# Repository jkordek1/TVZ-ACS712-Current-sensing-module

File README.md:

# TVZ ACS712 Current sensing module

 PCB module for ACS712, fully Integrated, Hall Effect-Based Linear Current Sensor with 2.1 kVRMS Voltage Isolation and a Low-Resistance Current Conductor.
 
 ## Features
 - 4mm banana plugs for sensors IP+ and IP- pins
 - 3 different capacitor values for filtering (switchable via jumper pins)
 - powering sensor via miniUSB or male pins
 - power LED
 - Probe clips for easy oscilloscope connections

## Images

## Project folder structure
    .
    ├── ...
    ├── Images                  # Images of the project
    ├── KiCADFiles              # Main folder
    │   ├── 3D models           # 3d models of components
    │   ├── Datasheet           # Datasheet collection
    │   ├── production          # gerber output folder
    │   ├── myDAQExpansionBoard # Main folder for KiCAD files
    │   └── Schematic.pdf       # Project schematic
    └── ...

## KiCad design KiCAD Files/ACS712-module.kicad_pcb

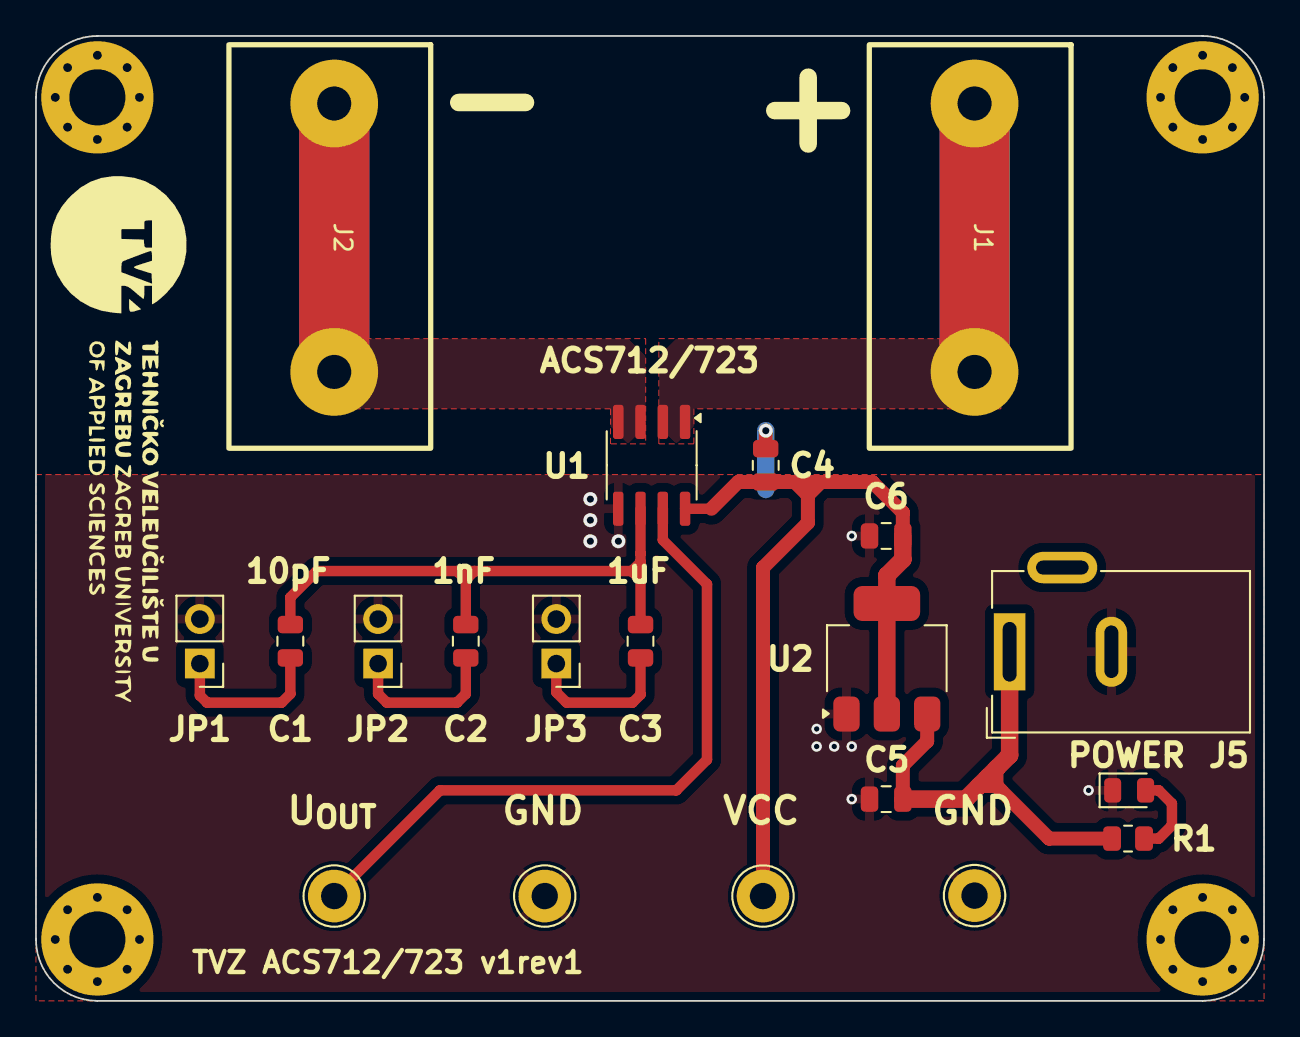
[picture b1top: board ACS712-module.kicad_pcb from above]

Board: 2 copper layers, 70.0 x 55.0 mm, 24 parts (0 on the bottom side), 11 nets.

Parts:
C1: 10p / 50V; C_0805_2012Metric
C2: 1n / 50V; C_0805_2012Metric
C3: 1u / 50V; C_0805_2012Metric
C4: 100n; C_0805_2012Metric
C5, C6: 10uF; C_0805_2012Metric
D1: RED; LED_0805_2012Metric
H1, H2, H3, H4: MountingHole_Pad; MountingHole_3.2mm_M3_Pad_Via
J1: Banana plug; DELTRON 4mm banana socket - red
J2: Banana plug; DELTRON 4mm banana socket - black
J5: Barrel_Jack_MountingPin; BarrelJack_Wuerth_6941xx301002
JP1, JP2, JP3: Jumper_2_Bridged; PinHeader_1x02_P2.54mm_Vertical
R1: 1k3; R_0805_2012Metric
TP1, TP2, TP3, TP4: TestPoint; KEYS4952
U1: ACS712; SOIC-8_3.9x4.9mm_P1.27mm
U2: AMS1117-5.0; SOT-223-3_TabPin2

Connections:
+5V: C4.1, C6.1, TP4.1, U1.8 (VCC), U2.2 (VO)
+12V: C5.1, J5.1, R1.1, U2.3 (VI)
/Vout: TP3.1, U1.7 (VIOUT)
GND: C4.2, C5.2, C6.2, D1.1 (K), J5.2, JP1.2 (B), JP2.2 (B), JP3.2 (B), TP1.1, TP2.1, U1.5 (GND), U2.1 (GND)
unnamed: D1.2 (A), R1.2
unnamed: J1.1, U1.1 (IP+), U1.2 (IP+)
unnamed: J2.1, U1.3 (IP-), U1.4 (IP-)
unnamed: C1.2, JP1.1 (A)
unnamed: C2.2, JP2.1 (A)
unnamed: C3.2, JP3.1 (A)
unnamed: C1.1, C2.1, C3.1, U1.6 (FILTER)

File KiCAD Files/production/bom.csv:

Designator,Footprint,Quantity,Value,LCSC Part #
C1,0805,1,10p / 50V,
C2,0805,1,1n / 50V,
C3,0805,1,1u / 50V,
C4,0805,1,100n,
"C5, C6",0805,2,10uF,
D1,0805,1,RED,
"H1, H2, H3, H4",MountingHole_3.2mm_M3_Pad_Via,4,MountingHole_Pad,
J1,DELTRON 4mm banana socket - red,1,Banana plug,
J2,DELTRON 4mm banana socket - black,1,Banana plug,
J5,BarrelJack_Wuerth_6941xx301002,1,Barrel_Jack_MountingPin,
"JP1, JP2, JP3",PinHeader_1x02_P2.54mm_Vertical,3,Jumper_2_Bridged,
R1,0805,1,1k3,
"TP1, TP2, TP3, TP4",KEYS4952,4,TestPoint,
U1,SOIC-8_3.9x4.9mm_P1.27mm,1,ACS712,
U2,SOT-223-3_TabPin2,1,AMS1117-5.0,

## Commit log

2024-08-24 test
